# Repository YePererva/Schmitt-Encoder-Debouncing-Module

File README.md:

# Rotary Encoder module with Hardware Debouncing
 Module to debounce incremental rotary encoder with Schmitt trigger

 Current Status: Layout finished, need to solder and test the hardware

This module uses 74xx14 Schmitt inverting trigger to debounce incremental rotary encoder.

The schematic in this module uses 74xx14 connected as buffer/repeater, according to 74xx14 [datasheet (Rev. J)](datasheets/sn74hc14(rev.j).pdf) from Texas Instruments (Figure 5 in Chapter 9.2: Typical Application). Later revisions don't have this circuit specified in datasheet.

## Dimensions and layout

- Overall dimensions : 1 in × 1 in (25.4 mm × 25.4 mm)
- Headers spacing : 0.9in × 0.1 in (22.86 mm × 2.54 mm)
- Mounting holes spacing : 0.8in × 0.8 in (20.32 mm × 20.32 mm)

| Dimensions & layout | Top view | Bottom view |
| ------------- | ------------- | ------------- |
|   |   |   |

The PCB was developed in 2 options, both are located within `project_files` folder:
- `0603` : utilizes resistors and capacitors in 0603 package (metric equivalent: 1608)
- `0805` : utilizes resistors and capacitors in 0805 package (metric equivalent: 2012)

## Why was it made?
I wanted to have a module for EC11 rotary encoder with push-button with some requirements:
- contains a built-in debouncing circuitry (both encoder and button)
- has symmetrical location of pin headers
- includes a few mounting holes for M2.5 screws
- utilizes SMD components and their single-side location (except of the encoder itself)
- the center of module matches the center of encoder rotation axis
- usable with breadboards
- could be soldered manually

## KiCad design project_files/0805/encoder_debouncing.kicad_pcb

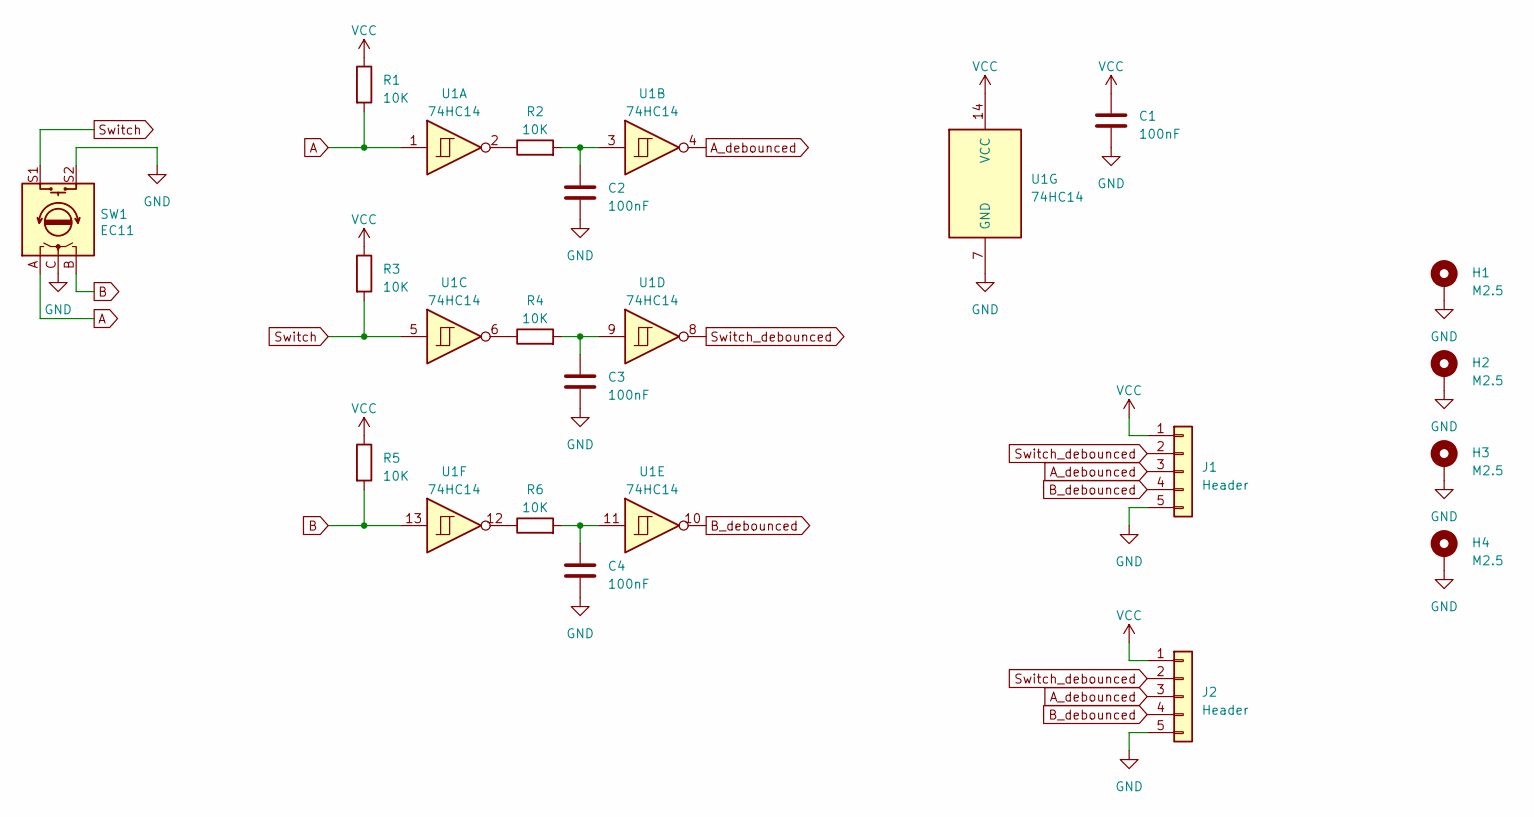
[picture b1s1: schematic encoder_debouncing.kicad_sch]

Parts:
C1, C2, C3, C4: 100nF; C_0805_2012Metric_Pad1.18x1.45mm_HandSolder
H1, H2, H3, H4: M2.5; MountingHole_2.7mm_M2.5_ISO7380_Pad_TopBottom
J1, J2: Header; PinHeader_1x05_P2.54mm_Vertical
R1, R2, R3, R4, R5, R6: 10K; R_0805_2012Metric_Pad1.20x1.40mm_HandSolder
SW1: EC11; RotaryEncoder_Alps_EC11E-Switch_Vertical_H20mm
U1: 74HC14; SOIC-14_3.9x8.7mm_P1.27mm

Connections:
A: R1.2, SW1.A, U1.1
A_debounced: J1.3, J2.3, U1.4
B: R5.2, SW1.B, U1.13
B_debounced: J1.4, J2.4, U1.10
GND: C1.2, C2.2, C3.2, C4.2, H1.1, H2.1, H3.1, H4.1, J1.5, J2.5, SW1.C, SW1.S2, U1.7 (GND)
unnamed: C2.1, R2.2, U1.3
unnamed: C3.1, R4.2, U1.9
unnamed: C4.1, R6.2, U1.11
unnamed: R2.1, U1.2
unnamed: R4.1, U1.6
unnamed: R6.1, U1.12
Switch: R3.2, SW1.S1, U1.5
Switch_debounced: J1.2, J2.2, U1.8
VCC: C1.1, J1.1, J2.1, R1.1, R3.1, R5.1, U1.14 (VCC)

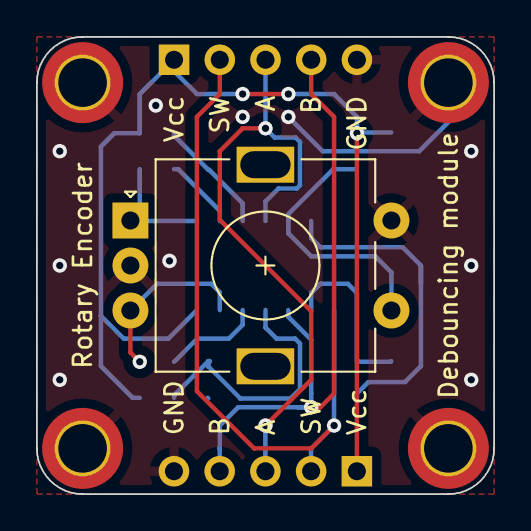
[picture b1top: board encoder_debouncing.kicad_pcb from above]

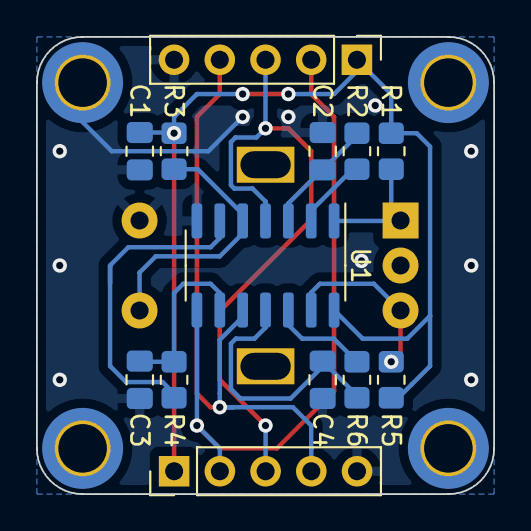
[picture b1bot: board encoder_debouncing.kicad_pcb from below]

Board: 2 copper layers, 25.4 x 25.4 mm, 18 parts (13 on the bottom side), 14 nets.

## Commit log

2021-07-06 project upload
2021-07-06 correction after DRC test
2021-07-07 values update
2021-07-08 added variation with 0805 components
2021-07-08 Edited description
2021-09-20 reopened with KiCad Nightly
2022-01-23 re-opened with KiCad 6.0.1
2022-04-03 Reopened in the last KiCad
